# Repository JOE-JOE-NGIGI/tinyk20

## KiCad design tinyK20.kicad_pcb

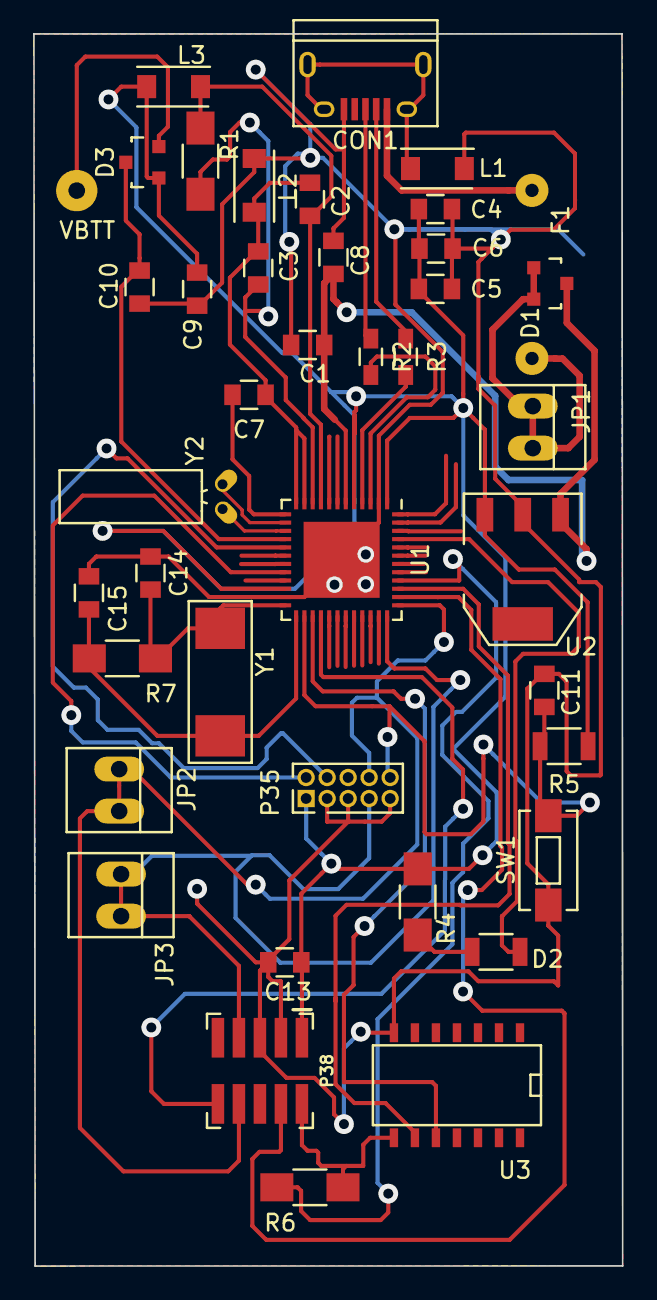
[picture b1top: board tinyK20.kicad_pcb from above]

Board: 2 copper layers, 35.6 x 74.5 mm, 41 parts (0 on the bottom side), 33 nets.

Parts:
C1, C3, C4, C5, C7, C8, C9, C10, C11, C13: 100n; C_0805
C2, C6: 2.2u; C_0805
C14, C15: 22nF; C_0805
CON1: USB-MINI-B; USB_Micro-B
D1, D3: BAS40-05; SOT-23
D2: LED; R_1206
F1: FUSE_F; WireConnection_0.80mmDrill
JP1, JP2, JP3: JUMPER_F; PINHEAD1-2
L1, L2, L3: INDUCTOR_F; Neosid_Inductor_SM1206
P35: CONN_5X2; Pin_Header_Straight_2x05_Pitch1.27mm
P38: CONN_5X2; CONN-2x5-1.27-SMT
R1: 470; R_1206_HandSoldering
R2, R3: 33; R_0603_HandSoldering
R4, R6: 1k; R_1206_HandSoldering
R5: 10k; R_1206
R7: 1M; R_1206_HandSoldering
SW1: SW_PUSH; SW_SPST_EVQPE1
U1: MK20DX128VFT5; QFN-48-1EP_7x7mm_Pitch0.5mm
U2: LT1129CST-3.3; SOT-223
U3: 74LS126; SOIC-14_N
VBTT: CONN_1; SolderWirePad_single_1mmDrill
Y1: Crystal; ABM3
Y2: Crystal_Small; Crystal_Round_Horizontal_3mm_BigPad

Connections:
3V3: C4.1, C5.1, C6.1, C9.1, C13.1, D3.1, L3.2, P35.1, P38.1, R4.1, R5.1, U1.1, U1.5, U1.22, U2.3
/D+: CON1.3, R2.1
/D-: CON1.2, R3.1
/x+: C15.2, R7.1, U1.25, Y1.2
/x-: C14.2, R7.2, U1.24, Y1.1
/xtal_N: U1.15, Y2.1
/xtal_P: U1.14, Y2.2
GND: C1.2, C4.2, C5.2, C6.2, C8.2, C9.2, C10.2, C11.2, C13.2, C14.1, C15.1, CON1.5, L1.1, L2.1, P35.3, P35.5, P35.9, P38.3, P38.5, SW1.1, U1.2, U1.23, U1.49, U2.2, U3.7
LED: D2.2, U1.45
unnamed: C2.1, L3.1, R1.1, U1.9
unnamed: C2.2, C3.2, C7.1, L2.2, U1.11, U1.12
unnamed: C3.1, R1.2, U1.10
unnamed: C7.2, U1.13
unnamed: C10.1, D3.3, U1.16
unnamed: CON1.6, L1.2
unnamed: D1.1, D1.2, F1.2, JP1.1, JP1.2
unnamed: D2.1, R4.2
unnamed: D3.2, VBTT.1
unnamed: P38.2, R6.2, U3.8
unnamed: R2.2, U1.3
unnamed: R3.2, U1.4
PTB0: U1.27, U3.10
PTB1: P38.10, U1.28
PTC5: P38.4, U1.38
PTC6: U1.39, U3.9
PTC7: R6.1, U1.40
RESET: C11.1, P35.10, R5.2, SW1.2, U1.26
SWD_CLK: P35.4, U1.17
SWD_IO: P35.2, U1.20
UART1_RX: JP3.1, JP3.2, P35.7, P38.7, U1.36
UART1_TX: JP2.1, JP2.2, P35.8, P38.8, U1.37
Vreg: CON1.1, F1.1
Vregin: C1.1, C8.1, D1.3, U1.6, U2.1

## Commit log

2016-04-05 change the connectors footprints to surface mount
2016-04-26 complete pin connections
2016-05-10 k20 schematic
    change the sd card socket
2016-05-14 update pcb
2016-05-14 Add files via upload
    add two 22nF capacitors and a 33M resistor to the crystal Y1
2016-05-17 Tiny k20 version 1
    add Design files
2016-08-08 Get rid of ground plane on top copper.
    Add optional vias. Re-route tracks
